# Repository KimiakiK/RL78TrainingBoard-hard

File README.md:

# RL78TrainingBoard-hard

## パーツリスト
- [RL78/G13 R5F100LJAFA 256KB/20KB](https://www.marutsu.co.jp/pc/i/166424/) x 1
- [1608角形チップ抵抗器 RK73B 27Ω 0.125W](https://www.marutsu.co.jp/pc/i/856811/) x 2

- [RL78/G13 R5F100LJAFA 256KB/20KB](https://akizukidenshi.com/catalog/g/gI-06179/) x 1
- [ＵＳＢシリアル変換ＩＣ　ＦＴ２３０ＸＳ](https://akizukidenshi.com/catalog/g/gI-13311/) x 1
- [ＲＳ２３２ＣインターフェースＩＣ　ＡＤＭ３２０２ＡＲＵＺ](https://akizukidenshi.com/catalog/g/gI-13704/) x 1
- [ＬＣＤキャラクタディスプレイモジュール（１６×２行バックライト付）](https://akizukidenshi.com/catalog/g/gP-00038/) x 1
- [ボックスヘッダ　１４Ｐ（２×７）](https://akizukidenshi.com/catalog/g/gC-10901/) x 1
- [ピンソケット（メス）　１×４（４Ｐ）](https://akizukidenshi.com/catalog/g/gC-10099/) x 2
- [Ｄサブコネクタ　９Ｐ　オス　基板取付用　Ｌタイプ　インチネジ](https://akizukidenshi.com/catalog/g/gC-00644/) x 1
- [表面実装圧電サウンダ　ＰＫＭＣＳ０９０９Ｅ４０００－Ｒ１](https://akizukidenshi.com/catalog/g/gP-14238/) x 1
- [表面実装用スピーカー　ＵＭ１５１５ＩＡ０８５００８](https://akizukidenshi.com/catalog/g/gP-06707/) x 1
- [ＮｃｈパワーＭＯＳＦＥＴ　３０Ｖ５．７Ａ　ＡＯ３４００Ａ](https://akizukidenshi.com/catalog/g/gI-14653/) x 1
- [８ｃｈソースタイプＤＭＯＳトランジスタアレイ　ＴＢＤ６２７８３ＡＦＧ](https://akizukidenshi.com/catalog/g/gI-11082/) x 1
- [オーディオアンプ HT82V739](http://akizukidenshi.com/catalog/g/gI-13356/) x 1
- [ヤマハ音源ＩＣ（ＹＭＺ２９４）](https://akizukidenshi.com/catalog/g/gI-12141/) x 1
- [チップ抵抗　１／１０Ｗ１００Ω　（５０００個入）](https://akizukidenshi.com/catalog/g/gR-14660/) x 2
- [チップ抵抗　１／１０Ｗ１ｋΩ　（５０００個入）](https://akizukidenshi.com/catalog/g/gR-14122/) x 11
- [チップ抵抗　１／１０Ｗ２．２ｋΩ　（５０００個入）](https://akizukidenshi.com/catalog/g/gR-16126/) x 3
- [チップ抵抗　１／１０Ｗ１０ｋΩ　（５０００個入）](https://akizukidenshi.com/catalog/g/gR-15029/) x 13
- [導電性高分子アルミ固体電解コンデンサー　ハイブリッド　１００μＦ２５Ｖ　ＰＦＶ](https://akizukidenshi.com/catalog/g/gP-14452/) x 1
- [チップ積層セラミックコンデンサー　０．１μＦ５０Ｖ　Ｆ　１６０８　（４０個入）](https://akizukidenshi.com/catalog/g/gP-13374/) x 12
- [チップ積層セラミックコンデンサー　０．０３９μＦ５０Ｖ　Ｂ　１６０８　（１００個入）](https://akizukidenshi.com/catalog/g/gP-05610/) x 2
- [チップ積層セラミックコンデンサー　１００μＦ１０Ｖ　Ｘ５Ｒ　３２１６　（１０個入）](https://akizukidenshi.com/catalog/g/gP-15633/) x 1
- [チップ積層セラミックコンデンサー　１０ｐＦ５０Ｖ　ＣＨ　１００５　（１００個入）](https://akizukidenshi.com/catalog/g/gP-13400/) x 2
- [チップ積層セラミックコンデンサー　１μＦ２５Ｖ　Ｘ７Ｒ　１６０８　（２０個入）](https://akizukidenshi.com/catalog/g/gP-14526/) x 3
- [黄緑色チップＬＥＤ　１６０８サイズ　ＳＭＬ－Ｅ１２Ｍ８ＷＴ８６　（１０個入）](https://akizukidenshi.com/catalog/g/gI-11877/) x 8
- [青色チップＬＥＤ　１６０８サイズ　ＳＭＬＥ１３ＢＣ８ＴＴ８６　（１０個入）](https://akizukidenshi.com/catalog/g/gI-11881) x 1
- [赤色チップＬＥＤ　１６０８　６３０ｎｍ　ＳＭＬ－Ｅ１２Ｖ８ＷＴ８６　（１０個入）](https://akizukidenshi.com/catalog/g/gI-11879) x 1
- [リセッタブルヒューズ　０．５Ａ　トリップ電流：１Ａ　耐圧：１３．２Ｖ　（４個入）](https://akizukidenshi.com/catalog/g/gP-15300/) x 1
- [チップインダクター（フェライトビーズ）　６０Ω［１６０８］　ムラタＢＬＭ１８Ｐ　（２５個入）](https://akizukidenshi.com/catalog/g/gP-04442/) x 1
- [表面実装型クリスタル（水晶発振子）　３２．７６８ｋＨｚ　（５個入）](https://akizukidenshi.com/catalog/g/gP-07195/) x 1
- [０．９６インチ　１２８×６４ドット有機ＥＬディスプレイ（ＯＬＥＤ）](https://akizukidenshi.com/catalog/g/gP-12031/) x 1
- [タクトスイッチ（赤色）](https://akizukidenshi.com/catalog/g/gP-03646/) x 1
- [タクトスイッチ（黄色）](https://akizukidenshi.com/catalog/g/gP-03650/) x 1
- [タクトスイッチ（緑色）](https://akizukidenshi.com/catalog/g/gP-03651/) x 1
- [タクトスイッチ（水色）](https://akizukidenshi.com/catalog/g/gP-03649/) x 1
- [タクトスイッチ（黒色）](https://akizukidenshi.com/catalog/g/gP-03647/) x 1
- [表面実装用タクトスイッチ　ＴＶＡＦ０６－Ａ０２０Ｂ－Ｒ　（５個入）](https://akizukidenshi.com/catalog/g/gP-14888/) x 1
- [半固定ボリューム　TSR-3386K　１０ｋΩ](https://akizukidenshi.com/catalog/g/gP-06110/) x 1
- [半固定ボリューム　TSR-3323S　１０ｋΩ](https://akizukidenshi.com/catalog/g/gP-13739/) x 1
- [基板取付用ボリューム　つまみ付き　薄型　１０ｋΩＡ　２連](https://akizukidenshi.com/catalog/g/gP-14734/) x 1
- [アナログジョイスティック](https://akizukidenshi.com/catalog/g/gP-04048/) x 1
- [照度センサ（フォトトランジスタ）　５６０ｎｍ　ＮＪＬ７５０２Ｌ　（２個入）](https://akizukidenshi.com/catalog/g/gI-02325/) x 1
- [高精度ＩＣ温度センサ　ＬＭ６０（ＳＯＴ－２３）　－２５～１２５℃　（５個入）](https://akizukidenshi.com/catalog/g/gI-02492/) x 1
- [基板用小型３Ｐトグルスイッチ　１回路２接点](https://akizukidenshi.com/catalog/g/gP-12406/) x 1
- [超小型スライドスイッチ　２回路２接点　ＩＳ－２２３５（４個入）](https://akizukidenshi.com/catalog/g/gP-02627/) x 1
- [ヒロセ表面実装用ＵＳＢコネクタ・ミニＢ・メス（４個入）](https://akizukidenshi.com/catalog/g/gC-05690/) x 1
- [チェック端子（テストポイント）　ＴＥＳＴ－３４](https://akizukidenshi.com/catalog/g/gP-12217/) x 1

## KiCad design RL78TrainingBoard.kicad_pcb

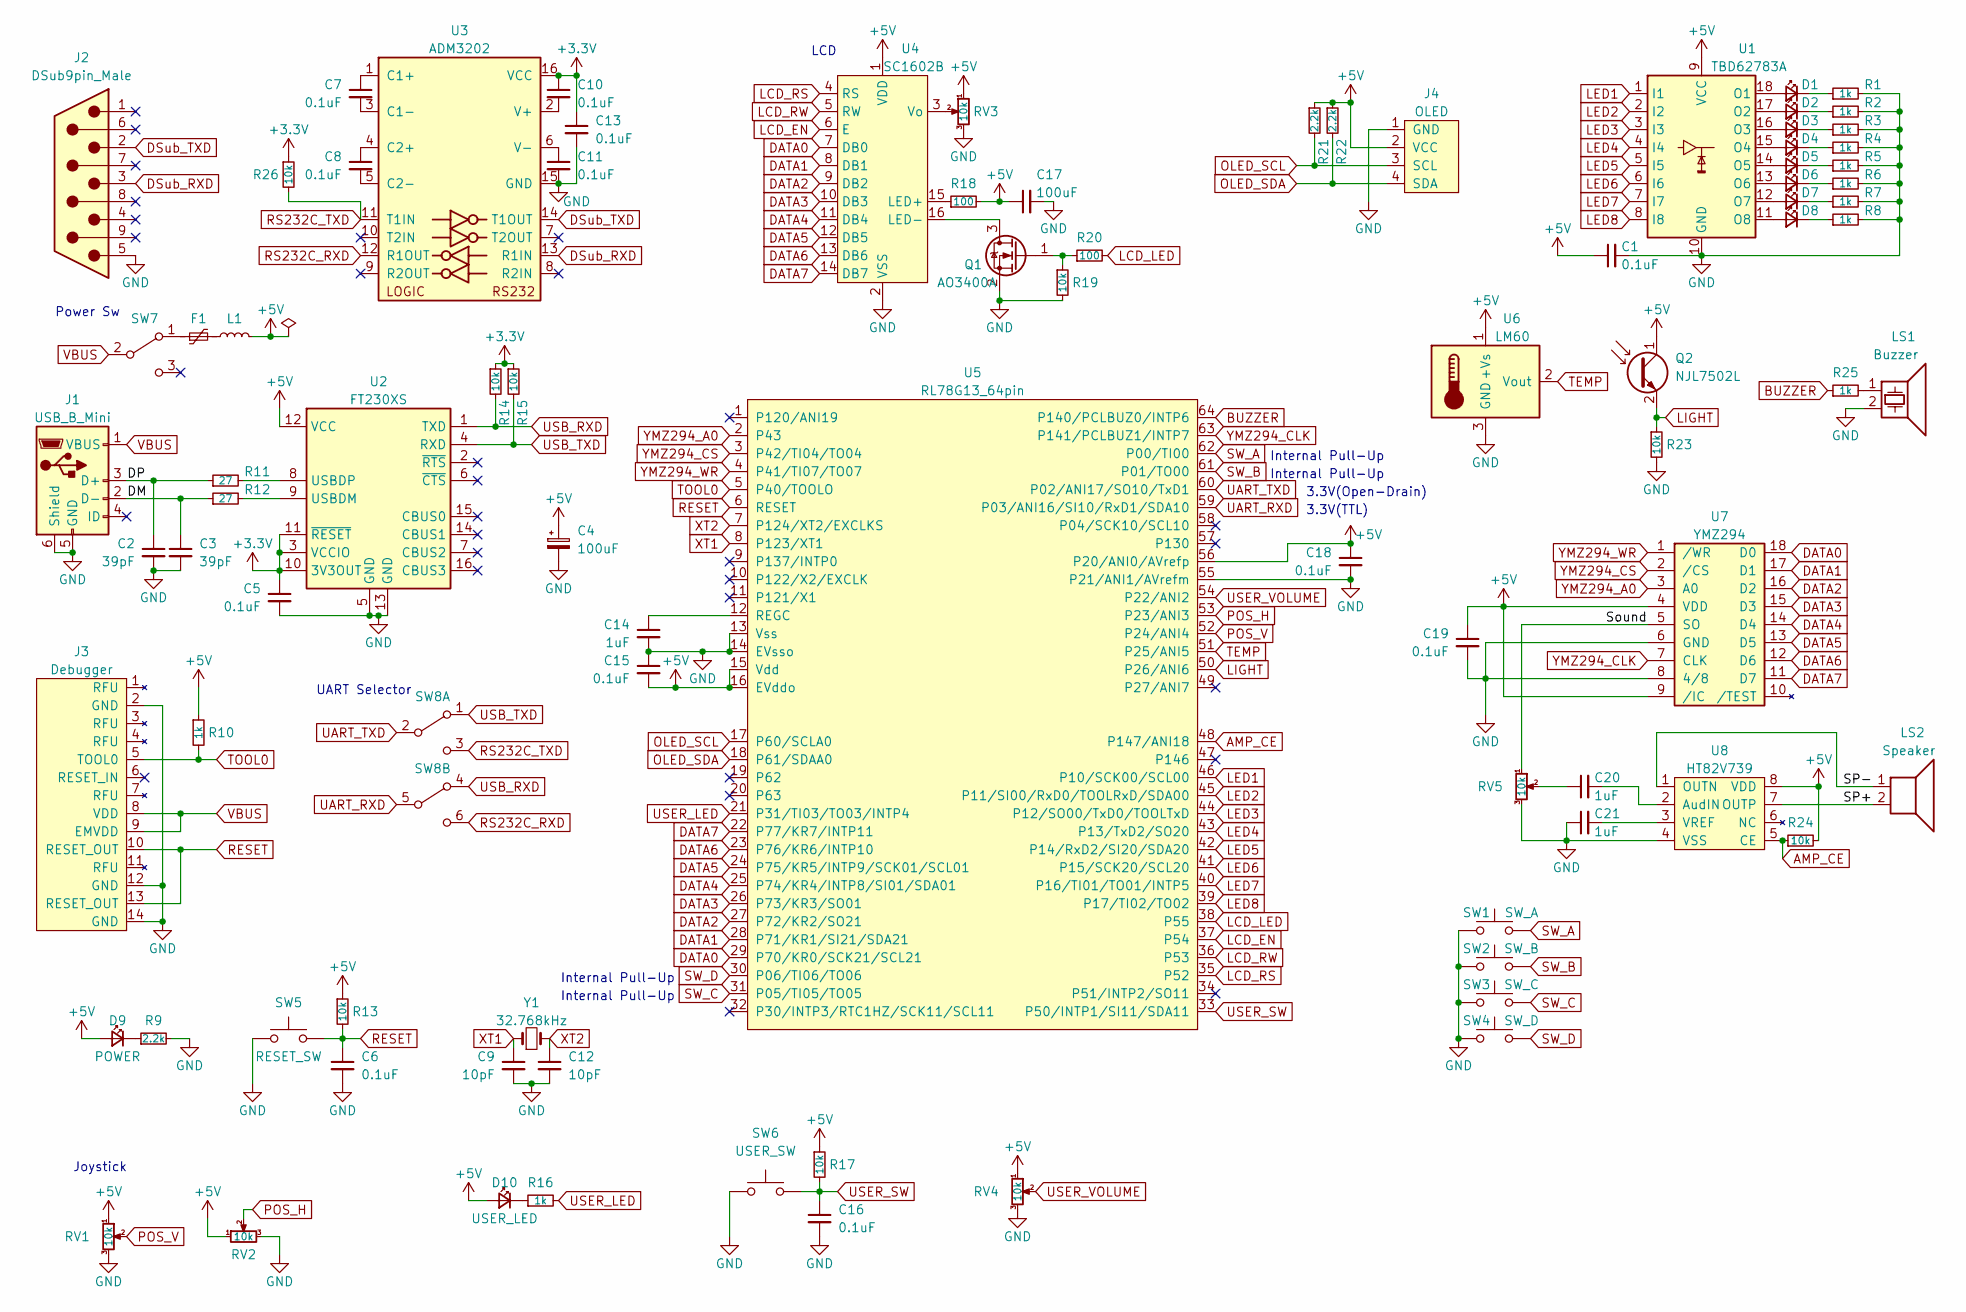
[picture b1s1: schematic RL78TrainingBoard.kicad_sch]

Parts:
C1, C5, C6, C7, C8, C10, C11, C13, C15, C16, C18, C19: 0.1uF; 1608Metric
C2, C3: 39pF; 1608Metric
C4: 100uF; CP_Elec_6.3x7.7
C9, C12: 10pF; 1005Metric
C14, C20, C21: 1uF; 1608Metric
C17: 100uF; 3216Metric
D1, D2, D3, D4, D5, D6, D7, D8: BYTE_LED; 1608Metric
D9: POWER; 1608Metric
D10: USER_LED; 1608Metric
F1: Polyfuse; 3216Metric
J1: USB_B_Mini; UX60SC-MB-5ST
J2: DSub9pin_Male; DSUB-9_Male_Horizontal_P2.77x2.84mm_EdgePinOffset7.70mm_Hou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
J3: Debugger; IDC-Header_2x07_P2.54mm_Vertical
J4: OLED
L1: L; 1608Metric
LS1: Buzzer; PKMCS0909E4000-R1
LS2: Speaker; UM1515IA085008
Q1: AO3400A; SOT-23
Q2: NJL7502L
R1, R2, R3, R4, R5, R6, R7, R8, R10, R16, R25: 1k; 1608Metric
R9, R21, R22: 2.2k; 1608Metric
R11, R12: 27; 1608Metric
R13, R14, R15, R17, R19, R23, R24, R26: 10k; 1608Metric
R18, R20: 100; 1608Metric
RV1, RV2: 10k; RV
RV3: 10k; TSR-3323S
RV4: 10k; TSR-3386K
RV5: 10k; Volume_RK10J
SW1: SW_A; SW_PUSH_6mm
SW2: SW_B; SW_PUSH_6mm
SW3: SW_C; SW_PUSH_6mm
SW4: SW_D; SW_PUSH_6mm
SW5: RESET_SW; SW_TVAF06
SW6: USER_SW; SW_PUSH_6mm
SW7: SW_SPDT; 2MS1-T2-B4-M2-Q-E-S
SW8: SW_DPDT_x2; IS-2235-G
U1: TBD62783A; SOP-18_7x12.5mm_P1.27mm
U2: FT230XS; SSOP-16_3.9x4.9mm_P0.635mm
U3: ADM3202; TSSOP-16-1EP_4.4x5mm_P0.65mm
U4: SC1602B; SC1602
U5: RL78G13_64pin; LQFP-64-12x12mm-P0.65mm_FusionPCB
U6: LM60; SOT-23
U7: YMZ294; DIP-18_W7.62mm_Socket
U8: HT82V739; SOP-8_3.9x4.9mm_P1.27mm
Y1: 32.768kHz; Crystal_SMD_3215-2Pin

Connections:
+3V3: C5.1, C10.1, C13.1, R14.1, R15.1, R26.1, U2.3 (VCCIO), U2.10 (3V3OUT), U2.11 (~RESET), U3.16 (VCC)
+5V: C1.1, C4.1, C15.2, C17.1, C18.1, C19.1, D9.2 (A), D10.2 (A), J4.2 (VCC), L1.2, Q2.1 (C), R10.1, R13.1, R17.1, R18.2, R21.1, R22.1, R24.2, RV1.1, RV2.1, RV3.1, RV4.1, U1.9 (VCC), U2.12 (VCC), U4.1 (VDD), U5.15 (Vdd), U5.16 (EVddo), U5.56 (P20/ANI0/AVrefp), U6.1 (+Vs), U7.4 (VDD), U7.9 (/IC), U8.8 (VDD)
/DM: C3.1, J1.2 (D-), R12.1
/DP: C2.1, J1.3 (D+), R11.1
/SP+: LS2.2, U8.7 (OUTP)
/SP-: LS2.1, U8.1 (OUTN)
/Sound: RV5.1, U7.5 (SO)
AMP_CE: R24.1, U5.48 (P147/ANI18), U8.5 (CE)
BUZZER: R25.1, U5.64 (P140/PCLBUZ0/INTP6)
DATA0: U4.7 (DB0), U5.29 (P70/KR0/SCK21/SCL21), U7.18 (D0)
DATA1: U4.8 (DB1), U5.28 (P71/KR1/SI21/SDA21), U7.17 (D1)
DATA2: U4.9 (DB2), U5.27 (P72/KR2/SO21), U7.16 (D2)
DATA3: U4.10 (DB3), U5.26 (P73/KR3/SO01), U7.15 (D3)
DATA4: U4.11 (DB4), U5.25 (P74/KR4/INTP8/SI01/SDA01), U7.14 (D4)
DATA5: U4.12 (DB5), U5.24 (P75/KR5/INTP9/SCK01/SCL01), U7.13 (D5)
DATA6: U4.13 (DB6), U5.23 (P76/KR6/INTP10), U7.12 (D6)
DATA7: U4.14 (DB7), U5.22 (P77/KR7/INTP11), U7.11 (D7)
DSub_RXD: J2.3, U3.13 (R1IN)
DSub_TXD: J2.2, U3.14 (T1OUT)
GND: C1.2, C2.2, C3.2, C4.2, C5.2, C6.2, C9.2, C11.2, C12.2, C13.2, C14.2, C15.1, C16.2, C17.2, C18.2, C19.2, C21.1, J1.5 (GND), J1.6 (Shield), J2.5, J3.2 (GND), J3.12 (GND), J3.14 (GND), J4.1 (GND), LS1.2, Q1.2 (S), R1.2, R2.2, R3.2, R4.2, R5.2, R6.2, R7.2, R8.2, R9.2, R19.2, R23.2, RV1.3, RV2.3, RV3.3, RV4.3, RV5.3, SW1.1, SW2.1, SW3.1, SW4.1, SW5.1, SW6.1, U1.10 (GND), U2.5 (GND), U2.13 (GND), U3.15 (GND), U4.2 (VSS), U5.13 (Vss), U5.14 (EVsso), U5.55 (P21/ANI1/AVrefm), U6.3 (GND), U7.6 (GND), U7.8 (4/8), U8.4 (VSS)
LCD_EN: U4.6 (E), U5.37 (P54)
LCD_LED: R20.2, U5.38 (P55)
LCD_RS: U4.4 (RS), U5.35 (P52)
LCD_RW: U4.5 (RW), U5.36 (P53)
LED1: U1.1 (I1), U5.46 (P10/SCK00/SCL00)
LED2: U1.2 (I2), U5.45 (P11/SI00/RxD0/TOOLRxD/SDA00)
LED3: U1.3 (I3), U5.44 (P12/SO00/TxD0/TOOLTxD)
LED4: U1.4 (I4), U5.43 (P13/TxD2/SO20)
LED5: U1.5 (I5), U5.42 (P14/RxD2/SI20/SDA20)
LED6: U1.6 (I6), U5.41 (P15/SCK20/SCL20)
LED7: U1.7 (I7), U5.40 (P16/TI01/TO01/INTP5)
LED8: U1.8 (I8), U5.39 (P17/TI02/TO02)
LIGHT: Q2.2 (E), R23.1, U5.50 (P26/ANI6)
unnamed: C7.1, U3.1 (C1+)
unnamed: C7.2, U3.3 (C1-)
unnamed: C8.1, U3.4 (C2+)
unnamed: C8.2, U3.5 (C2-)
unnamed: C10.2, U3.2 (V+)
unnamed: C11.1, U3.6 (V-)
unnamed: C14.1, U5.12 (REGC)
unnamed: C20.1, RV5.2
unnamed: C20.2, U8.2 (AudIN)
unnamed: C21.2, U8.3 (VREF)
unnamed: D1.1 (K), R1.1
unnamed: D1.2 (A), U1.18 (O1)
unnamed: D2.1 (K), R2.1
unnamed: D2.2 (A), U1.17 (O2)
unnamed: D3.1 (K), R3.1
unnamed: D3.2 (A), U1.16 (O3)
unnamed: D4.1 (K), R4.1
unnamed: D4.2 (A), U1.15 (O4)
unnamed: D5.1 (K), R5.1
unnamed: D5.2 (A), U1.14 (O5)
unnamed: D6.1 (K), R6.1
unnamed: D6.2 (A), U1.13 (O6)
unnamed: D7.1 (K), R7.1
unnamed: D7.2 (A), U1.12 (O7)
unnamed: D8.1 (K), R8.1
unnamed: D8.2 (A), U1.11 (O8)
unnamed: D9.1 (K), R9.1
unnamed: D10.1 (K), R16.1
unnamed: F1.1, SW7.1 (A)
unnamed: F1.2, L1.1
unnamed: LS1.1, R25.2
unnamed: Q1.1 (G), R19.1, R20.1
unnamed: Q1.3 (D), U4.16 (LED-)
unnamed: R11.2, U2.8 (USBDP)
unnamed: R12.2, U2.9 (USBDM)
unnamed: R18.1, U4.15 (LED+)
unnamed: RV3.2, U4.3 (Vo)
OLED_SCL: J4.3 (SCL), R21.2, U5.17 (P60/SCLA0)
OLED_SDA: J4.4 (SDA), R22.2, U5.18 (P61/SDAA0)
POS_H: RV2.2, U5.53 (P23/ANI3)
POS_V: RV1.2, U5.52 (P24/ANI4)
RESET: C6.1, J3.10 (RESET_OUT), J3.13 (RESET_OUT), R13.2, SW5.2, U5.6 (RESET)
RS232C_RXD: SW8.6 (C), U3.12 (R1OUT)
RS232C_TXD: R26.2, SW8.3 (C), U3.11 (T1IN)
SW_A: SW1.2, U5.62 (P00/TI00)
SW_B: SW2.2, U5.61 (P01/TO00)
SW_C: SW3.2, U5.31 (P05/TI05/TO05)
SW_D: SW4.2, U5.30 (P06/TI06/TO06)
TEMP: U5.51 (P25/ANI5), U6.2 (Vout)
TOOL0: J3.5 (TOOL0), R10.2, U5.5 (P40/TOOLO)
UART_RXD: SW8.5 (B), U5.59 (P03/ANI16/SI10/RxD1/SDA10)
UART_TXD: SW8.2 (B), U5.60 (P02/ANI17/SO10/TxD1)
USB_RXD: R14.2, SW8.4 (A), U2.1 (TXD)
USB_TXD: R15.2, SW8.1 (A), U2.4 (RXD)
USER_LED: R16.2, U5.21 (P31/TI03/TO03/INTP4)
USER_SW: C16.1, R17.2, SW6.2, U5.33 (P50/INTP1/SI11/SDA11)
USER_VOLUME: RV4.2, U5.54 (P22/ANI2)
VBUS: J1.1 (VBUS), J3.8 (VDD), J3.9 (EMVDD), SW7.2 (B)
XT1: C9.1, U5.8 (P123/XT1), Y1.1
XT2: C12.1, U5.7 (P124/XT2/EXCLKS), Y1.2
YMZ294_A0: U5.2 (P43), U7.3 (A0)
YMZ294_CLK: U5.63 (P141/PCLBUZ1/INTP7), U7.7 (CLK)
YMZ294_CS: U5.3 (P42/TI04/TO04), U7.2 (/CS)
YMZ294_WR: U5.4 (P41/TI07/TO07), U7.1 (/WR)

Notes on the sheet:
3.3V(Open-Drain)
LCD
3.3V(TTL)
Internal Pull-Up
Joystick
UART Selector
Power Sw

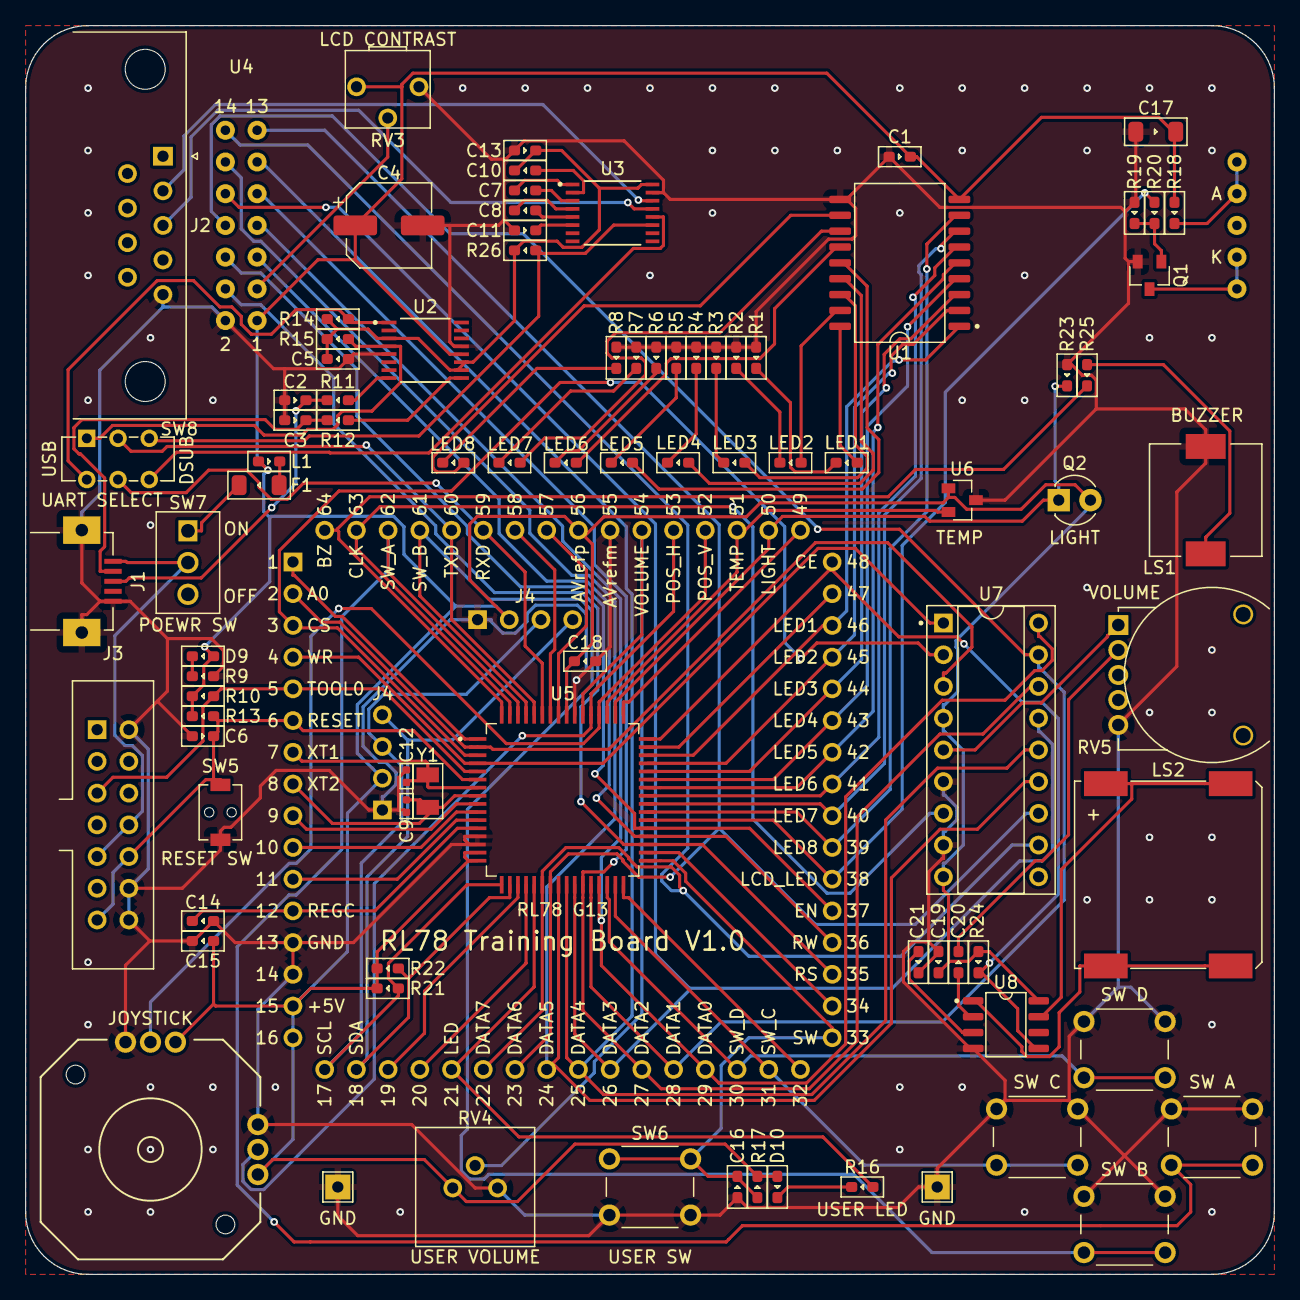
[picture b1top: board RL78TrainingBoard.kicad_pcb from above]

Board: 2 copper layers, 100.0 x 100.0 mm, 89 parts (0 on the bottom side), 97 nets.

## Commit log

2022-05-22 回路図ドラフト版作成
2022-05-23 フットプリント作成
2022-05-24 基板設計(部品仮配置)
2022-05-25 部品見直し
2022-05-25 基板設計(部品配置)
2022-05-26 配線作成
2022-05-27 基板 V1.0
2022-05-30 パーツリスト更新
